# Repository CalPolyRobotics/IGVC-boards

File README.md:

# IGVC-boards
IGVC schematic and board files

.gitignore is set to only allow uploads of .sch, .brd, and .lib files.

Do not modify folders with "Final" in the name.

Pro tips:

1. Clone this repository to your computer. You need git.

2. In Eagle, go to Options > Directories.

3. Click in the "Projects" text field and then the "Browse" button to choose a directory.

4. Select the "IGVC-boards" directory that you cloned from git.

5. Click "OK" and you should see the directory in the "Projects" list in Eagle Control Panel.

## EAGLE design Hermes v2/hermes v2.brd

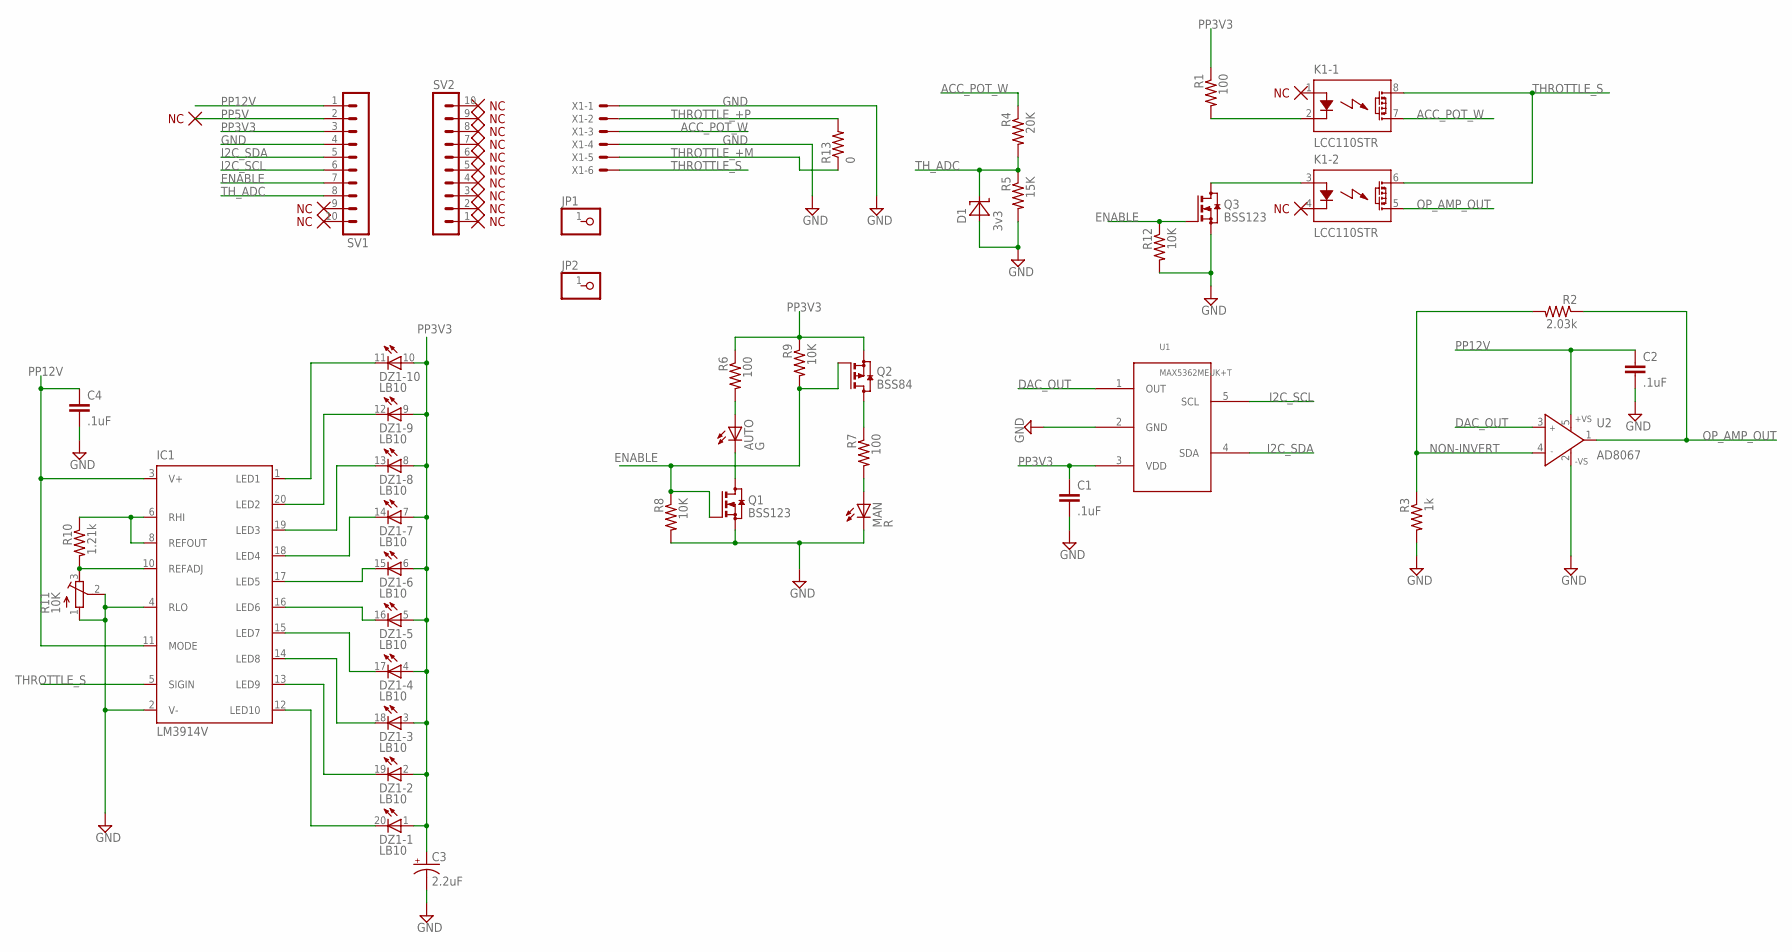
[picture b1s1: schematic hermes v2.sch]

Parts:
AUTO: G; LED_SML0603
C1, C2, C4: .1uF; C0402
C3: 2.2uF; SMC_A; DIGI 478-3119-2-ND
D1: 3v3; SOD323_ST
DZ1: LB10
IC1: LM3914V; PLCC20S
JP1, JP2: PINHD-1X1; 1X01
K1: LCC110STR; DIL08SMD
MAN: R; LED_SML0603
Q1, Q3: BSS123; SOT23
Q2: BSS84; SOT23
R1, R6, R7: 100; R0603
R2: 2.03k; R0603
R3: 1k; R0603
R4: 20K; R0603
R5: 15K; R0603
R8, R9, R12: 10K; R0603
R10: 1.21k; R0603
R11: 10K; RTRIM5X; DIGI 490-2678-1-ND
R13: 0; R0402
SV1, SV2: MA10-1
U1: DAC; SOT23-5
U2: AD8067; SOT23-5; DIGI 497-13051-1-ND
X1: 22-23-2061

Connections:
ACC_POT_W: K1.7 (D2), R4.1, X1.3
CONTROL_+: K1.2 (K), R1.2
CONTROL_-: K1.3 (A), Q3.3 (D)
DAC_OUT: U1.1 (OUT), U2.3 (IN+)
ENABLE: Q1.1 (G), Q2.1 (G), Q3.1 (G), R8.1, R9.2, R12.1, SV1.7
GND: C1.2, C2.2, C3.-, C4.2, D1.A, IC1.2 (V-), IC1.4 (RLO), MAN.C, Q1.2 (S), Q3.2 (S), R3.2, R5.2, R8.2, R11.1 (A), R11.2 (S), R12.2, SV1.4, U1.2 (GND), U2.2 (-VS), X1.1, X1.4
I2C_SCL: SV1.6, U1.5 (SCL)
I2C_SDA: SV1.5, U1.4 (SDA)
unnamed: DZ1.11 (C), IC1.1 (LED1)
unnamed: AUTO.C, Q1.3 (D)
unnamed: MAN.A, R7.2
unnamed: AUTO.A, R6.2
unnamed: Q2.3 (D), R7.1
unnamed: DZ1.12 (C), IC1.20 (LED2)
unnamed: DZ1.13 (C), IC1.19 (LED3)
unnamed: DZ1.14 (C), IC1.18 (LED4)
unnamed: DZ1.15 (C), IC1.17 (LED5)
unnamed: DZ1.16 (C), IC1.16 (LED6)
unnamed: DZ1.17 (C), IC1.15 (LED7)
unnamed: DZ1.18 (C), IC1.14 (LED8)
unnamed: DZ1.19 (C), IC1.13 (LED9)
unnamed: DZ1.20 (C), IC1.12 (LED10)
unnamed: IC1.10 (REFADJ), R10.2, R11.3 (E)
unnamed: IC1.6 (RHI), IC1.8 (REFOUT), R10.1
NON-INVERT: R2.2, R3.1, U2.4 (IN-)
OP_AMP_OUT: K1.5 (D2), R2.1, U2.1 (OUT)
PP3V3: C1.1, C3.+, DZ1.1 (A), DZ1.2 (A), DZ1.3 (A), DZ1.4 (A), DZ1.5 (A), DZ1.6 (A), DZ1.7 (A), DZ1.8 (A), DZ1.9 (A), DZ1.10 (A), Q2.2 (S), R1.1, R6.1, R9.1, SV1.3, U1.3 (VDD)
PP5V: SV1.2
PP12V: C2.1, C4.1, IC1.3 (V+), IC1.11 (MODE), SV1.1, U2.5 (+VS)
THROTTLE_+M: R13.1, X1.5
THROTTLE_+P: R13.2, X1.2
THROTTLE_S: IC1.5 (SIGIN), K1.6 (D1), K1.8 (D1), X1.6
TH_ADC: D1.C, R4.2, R5.1, SV1.8

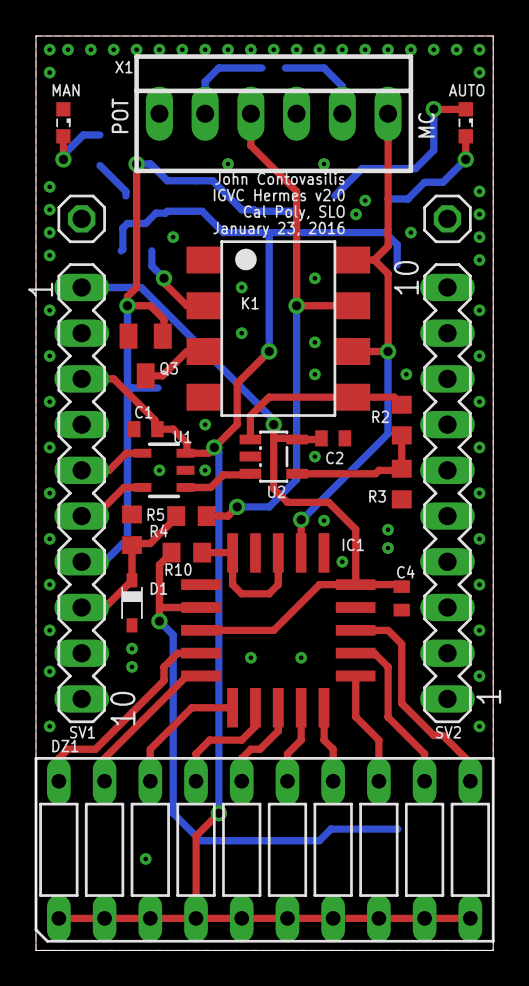
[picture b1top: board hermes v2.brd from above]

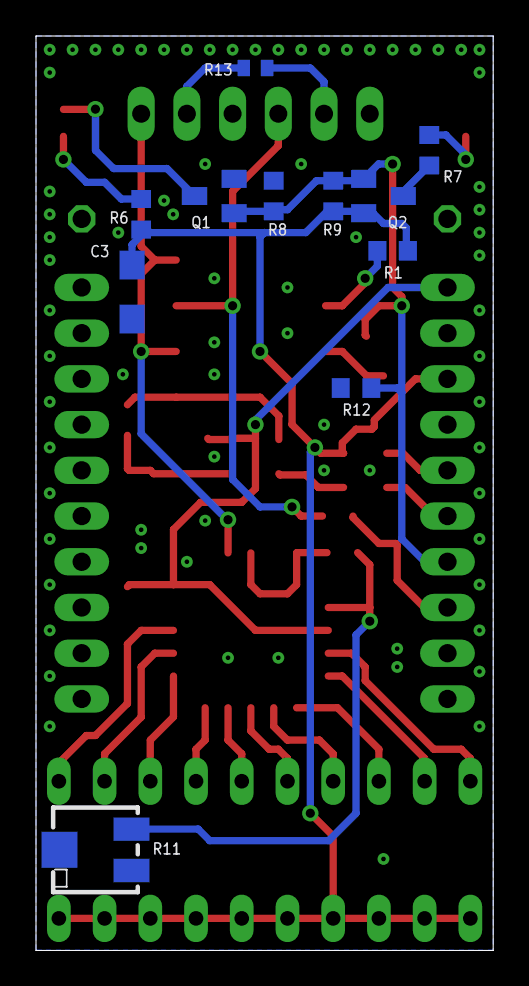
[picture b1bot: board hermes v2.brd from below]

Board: 2 copper layers, 25.4 x 50.8 mm, 33 parts (11 on the bottom side), 32 nets.

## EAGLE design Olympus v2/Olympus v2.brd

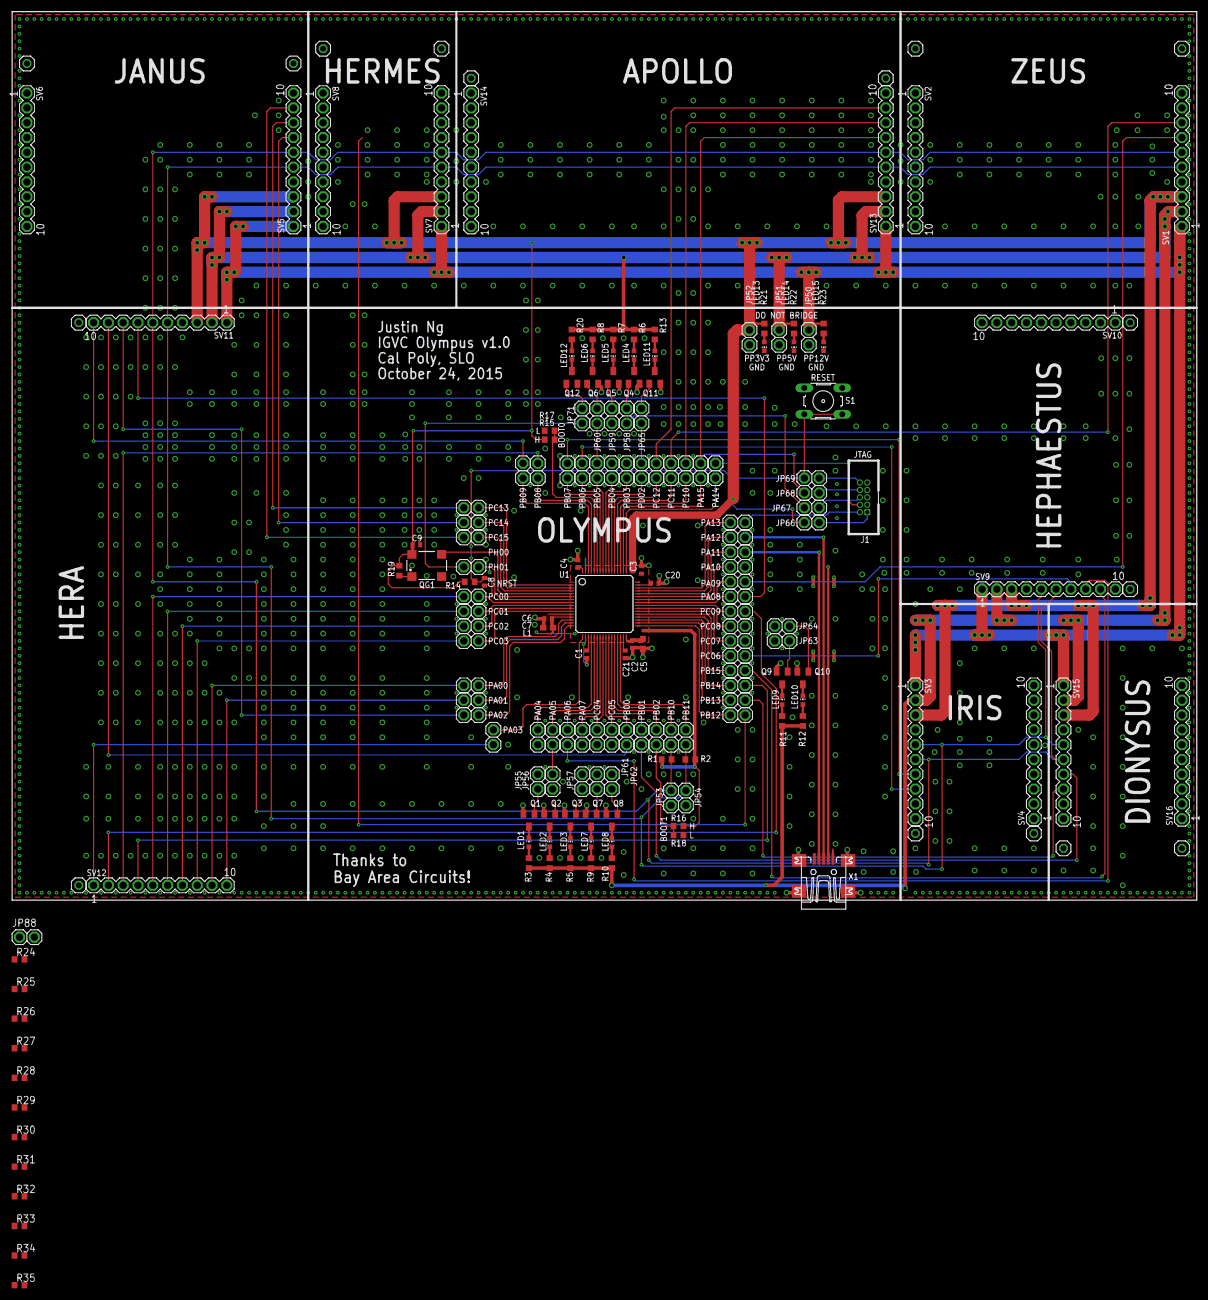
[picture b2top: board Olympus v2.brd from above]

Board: 2 copper layers, 203.2 x 152.4 mm, 183 parts (0 on the bottom side), 144 nets.

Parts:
C1, C2, C3, C4, C6, C8, C9: 0.1uF; C0402
C5: 4.7uF; C0603
C7: 1uF; C0603
C20, C21: 2.2uF; C0402
J1: HEADER_10P_0.05
JP1, JP2, JP3, JP4, JP5, JP6, JP7, JP8, JP9, JP10, JP11, JP12, JP13, JP14, JP15, JP16, JP17, JP18, JP19, JP20, JP21, JP22, JP23, JP24, JP25, JP26, JP27, JP28, JP29, JP30, JP31, JP32, JP33, JP34, JP35, JP36, JP37, JP38, JP39, JP40, JP41, JP42, JP43, JP44, JP45, JP46, JP47, JP48, JP49, JP50, JP51, JP52, JP53, JP54, JP55, JP56, JP57, JP58, JP59, JP60, JP61, JP62, JP63, JP64, JP65, JP66, JP67, JP68, JP69, JP70, JP71, JP88: 1X02
JP72, JP73, JP74, JP75, JP76, JP77, JP78, JP79, JP80, JP81, JP82, JP83, JP84, JP85, JP86, JP87: 1X01
L1: L0201
LED1, LED2, LED3, LED4, LED5, LED6, LED7, LED8, LED9, LED10, LED11, LED12, LED13, LED14, LED15: CHIP-LED0603
Q1, Q2, Q3, Q4, Q5, Q6, Q7, Q8, Q9, Q10, Q11, Q12: BSS138; SOT23
QG1: KC7050A20.0000C3GE00; SM77H
R1, R2: 3.3k; R0603
R3, R4, R5, R6, R7, R8, R9, R10, R11, R12, R13, R20: 1k; R0603
R14, R15, R16, R17, R18, R19, R24, R25, R26, R27, R28, R29, R30, R31, R32, R33, R34, R35: 10k; R0603
R21: 82; R0603
R22: 200; R0603
R23: 680; R0603
S1: B3F-10XX
SV1, SV2, SV3, SV4, SV5, SV6, SV7, SV8, SV9, SV10, SV11, SV12, SV13, SV14, SV15, SV16: MA10-1
U1: STM32F205RGT6; LQFP-ST-64-2
X1: MINI-USB-UX60-MB-5ST; UX60-MB-5ST

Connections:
APOLLO_SPI_MOSI: JP45.2, SV13.9
APOLLO_SPI_SCK: JP43.2, SV13.8
APOLLO_SPI_SS_N: JP16.1, JP68.2, SV13.7
DIONYSUS_BRD_EN: JP18.1, SV15.7
DIONYSUS_GPIO: JP30.1, SV15.8
GND: C1.2, C2.2, C3.2, C4.2, C5.2, C6.2, C7.2, C8.2, C9.2, C20.2, C21.2, J1.3, J1.5, JP50.2, JP51.2, JP52.2, JP53.2, JP54.2, LED13.C, LED14.C, LED15.C, Q1.2, Q2.2, Q3.2, Q4.2, Q5.2, Q6.2, Q7.2, Q8.2, Q9.2, Q10.2, Q11.2, Q12.2, QG1.2, R17.1, R18.1, R24.2, R25.2, R26.2, R27.2, R28.2, R29.2, R30.2, R31.2, R32.2, R33.2, R34.2, R35.2, S1.3, S1.4, SV1.4, SV3.4, SV5.4, SV7.4, SV9.4, SV11.4, SV13.4, SV15.4, U1.12, U1.18, U1.63, X1.5
HEPHAESTUS_DIR: JP39.2, SV9.7
HEPHAESTUS_GPIO: JP32.1, SV9.9
HEPHAESTUS_SPD: JP7.1, SV9.8
HERA_HALL1: JP25.1, SV12.3
HERA_HALL2: JP31.1, JP42.2, SV12.4
HERA_SONAR1: JP9.1, SV11.7
HERA_SONAR2: JP3.1, SV11.8
HERA_SONAR3: JP17.1, SV11.9
HERA_SONAR4: JP26.1, SV11.10
HERA_SONAR5: JP4.1, SV12.1
HERA_STEER: JP33.2, SV12.5
HERA_TEMP1: JP34.2, SV12.6
HERA_TEMP2: JP35.2, SV12.7
HERA_TEMP3: JP36.2, SV12.8
HERA_TEMP4: JP1.1, SV12.9
HERA_TEMP5: JP2.1, SV12.10
I2C_SCL: JP27.1, JP53.1, R1.1, SV1.6, SV3.6, SV5.6, SV7.6, SV9.6, SV11.6, SV13.6, SV15.6
I2C_SDA: JP28.1, JP54.1, R2.1, SV1.5, SV3.5, SV5.5, SV7.5, SV9.5, SV11.5, SV13.5, SV15.5
IRIS_UART_RX: JP24.1, SV3.7
IRIS_UART_TX: JP23.1, SV3.8
JANUS_AUTOMAN: JP48.2, SV5.9
JANUS_F: JP47.2, SV5.7
JANUS_R: JP46.2, SV5.8
JTAG_NRST: J1.10, JP69.1
JTAG_SWO: J1.6, JP67.1
JTAG_TDI: J1.8, JP68.1
JTAG_VREF: J1.1, JP66.2
LED1_A: LED1.A, R3.1
LED1_C: LED1.C, Q1.3
LED1_G: JP55.1, Q1.1, R24.1
LED2_A: LED2.A, R4.1
LED2_C: LED2.C, Q2.3
LED2_G: JP56.1, Q2.1, R25.1
LED3_A: LED3.A, R5.1
LED3_C: LED3.C, Q3.3
LED3_G: JP57.1, Q3.1, R26.1
LED4_A: LED4.A, R6.1
LED4_C: LED4.C, Q4.3
LED4_G: JP58.1, Q4.1, R27.1
LED5_A: LED5.A, R7.1
LED5_C: LED5.C, Q5.3
LED5_G: JP59.1, Q5.1, R32.1
LED6_A: LED6.A, R8.1
LED6_C: LED6.C, Q6.3
LED6_G: JP60.1, Q6.1, R33.1
LED7_A: LED7.A, R9.1
LED7_C: LED7.C, Q7.3
LED7_G: JP61.1, Q7.1, R34.1
LED8_A: LED8.A, R10.1
LED8_C: LED8.C, Q8.3
LED8_G: JP62.1, Q8.1, R35.1
LED9_A: LED9.A, R11.1
LED9_C: LED9.C, Q9.3
LED9_G: JP63.1, Q9.1, R28.1
LED10_A: LED10.A, R12.1
LED10_C: LED10.C, Q10.3
LED10_G: JP64.1, Q10.1, R29.1
LED11_A: LED11.A, R13.1
LED11_C: LED11.C, Q11.3
LED11_G: JP65.1, Q11.1, R30.1
LED12_A: LED12.A, R20.1
LED12_C: LED12.C, Q12.3
LED12_G: JP71.1, Q12.1, R31.1
LED13_R: LED13.A, R21.1
LED14_R: LED14.A, R22.1
LED15_R: LED15.A, R23.1
MCU_BOOT0: JP88.1, R15.1, R17.2, U1.60
MCU_BOOT1: JP19.1, R16.1, R18.2
MCU_NRST: C8.1, JP69.2, R14.1, S1.1, S1.2, U1.7
MCU_PA0: JP1.2, U1.14
MCU_PA1: JP2.2, U1.15
MCU_PA2: JP3.2, U1.16
MCU_PA3: JP4.2, U1.17
MCU_PA4: JP5.2, U1.20
MCU_PA5: JP6.2, U1.21
MCU_PA6: JP7.2, U1.22
MCU_PA7: JP8.2, U1.23
MCU_PA8: JP9.2, U1.41
MCU_PA9: JP10.2, U1.42
MCU_PA10: JP11.2, U1.43
MCU_PA11: JP12.2, U1.44
MCU_PA12: JP13.2, U1.45
MCU_PA13: JP14.2, U1.46
MCU_PA14: JP15.2, U1.49
MCU_PA15: JP16.2, U1.50
MCU_PB0: JP17.2, U1.26
MCU_PB1: JP18.2, U1.27
MCU_PB2: JP19.2, U1.28
MCU_PB3: JP20.2, U1.55
MCU_PB4: JP21.2, U1.56
MCU_PB5: JP22.2, U1.57
MCU_PB6: JP23.2, U1.58
MCU_PB7: JP24.2, U1.59
MCU_PB8: JP25.2, U1.61
MCU_PB9: JP26.2, U1.62
MCU_PB10: JP27.2, U1.29
MCU_PB11: JP28.2, U1.30
MCU_PB12: JP29.2, U1.33
MCU_PB13: JP30.2, U1.34
MCU_PB14: JP31.2, U1.35
MCU_PB15: JP32.2, U1.36
MCU_PC0: JP33.1, U1.8
MCU_PC1: JP34.1, U1.9
MCU_PC2: JP35.1, U1.10
MCU_PC3: JP36.1, U1.11
MCU_PC4: JP37.1, U1.24
MCU_PC5: JP38.1, U1.25
MCU_PC6: JP39.1, U1.37
MCU_PC7: JP40.1, U1.38
MCU_PC8: JP41.1, U1.39
MCU_PC9: JP42.1, U1.40
MCU_PC10: JP43.1, U1.51
MCU_PC11: JP44.1, U1.52
MCU_PC12: JP45.1, U1.53
MCU_PC13: JP46.1, U1.2
MCU_PC14: JP47.1, U1.3
MCU_PC15: JP48.1, U1.4
MCU_PD2: JP49.1, U1.54
MCU_PH0: QG1.3, U1.5
MCU_PH1: JP70.1, U1.6
MCU_VCAP_1: C21.1, U1.31
MCU_VCAP_2: C20.1, U1.47
OLYMPUS_GPIO2: JP6.1, JP56.2
OLYMPUS_GPIO4: JP58.2, JP67.2
OLYMPUS_GPIO6: JP22.1, JP60.2
OLYMPUS_GPIO11: JP49.2, JP65.2
OLYMPUS_GPIO12: JP70.2, JP71.2
OLYMPUS_SWDCLK: J1.4, JP15.1
OLYMPUS_SWDIO: J1.2, JP14.1
OLYMPUS_USBDN: JP12.1, X1.2
OLYMPUS_USBDP: JP13.1, X1.3
OSC_EN: QG1.1, R19.1
PP3V3: C1.1, C2.1, C3.1, C4.1, C5.1, C9.1, JP52.1, JP66.1, L1.2, QG1.4, R1.2, R2.2, R14.2, R15.2, R16.2, R19.2, R21.2, SV1.3, SV3.3, SV5.3, SV7.3, SV9.3, SV11.3, SV13.3, SV15.3, U1.19, U1.32, U1.48, U1.64
PP3V3A: C6.1, C7.1, L1.1, U1.13
PP5V: JP51.1, R3.2, R4.2, R5.2, R6.2, R7.2, R8.2, R9.2, R10.2, R11.2, R12.2, R13.2, R20.2, R22.2, SV1.2, SV3.2, SV5.2, SV7.2, SV9.2, SV11.2, SV13.2, SV15.2
PP12V: JP50.1, R23.2, SV1.1, SV3.1, SV5.1, SV7.1, SV9.1, SV11.1, SV13.1, SV15.1
ZEUS_GPIO: JP44.2, SV1.8
ZEUS_SHUTDOWN_N: JP10.1, SV1.7

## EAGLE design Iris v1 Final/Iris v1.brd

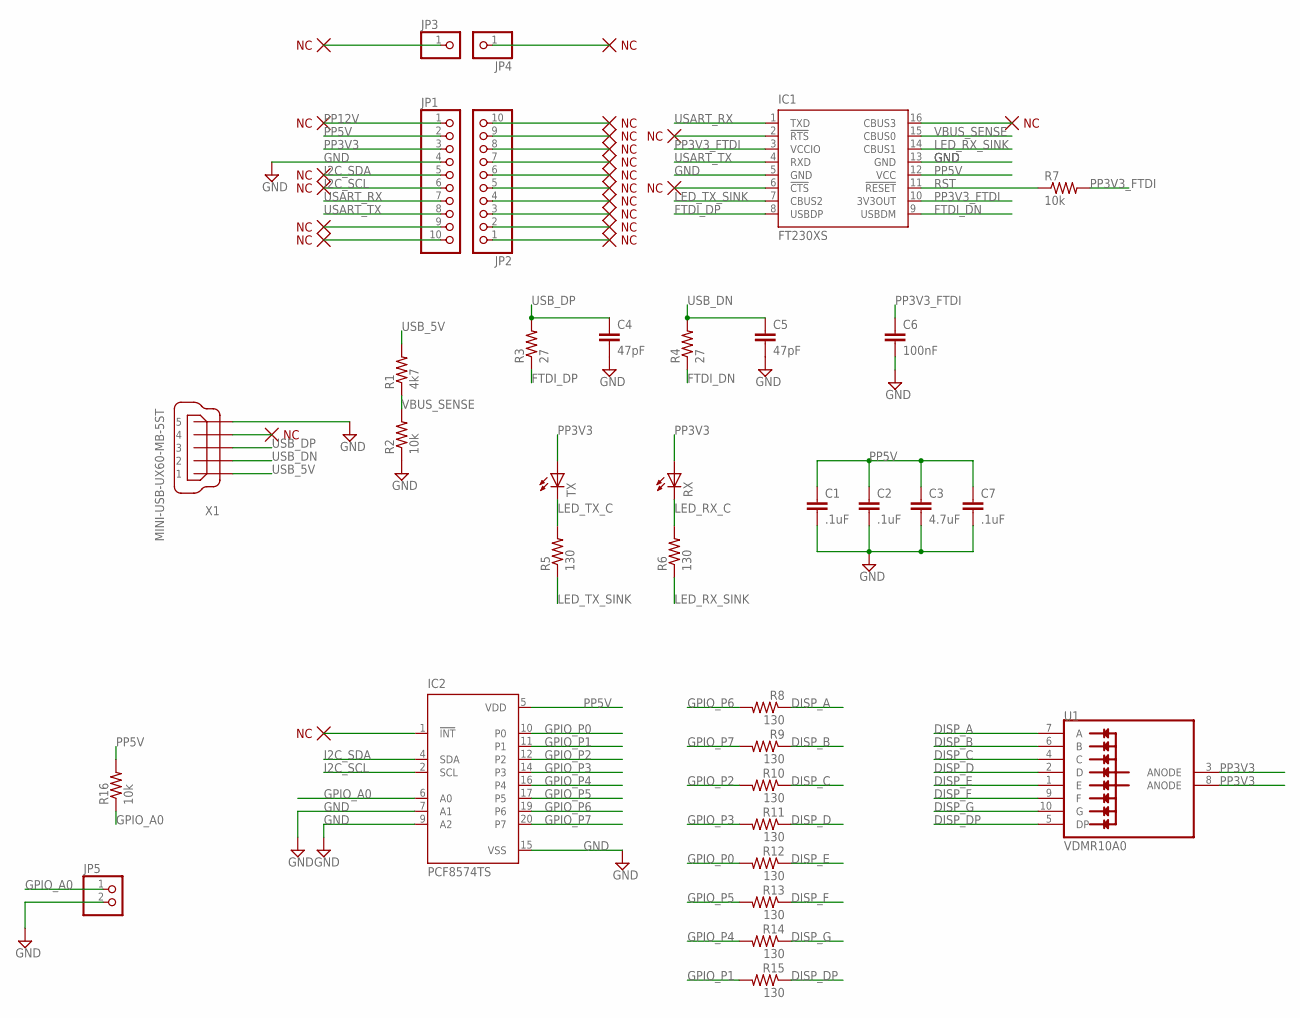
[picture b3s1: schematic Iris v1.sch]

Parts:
C1, C2, C7: .1uF; C0402
C3: 4.7uF; C0603
C4, C5: 47pF; C0402
C6: 100nF; C0402
IC1: FT230XS; SSOP16; DIGI 768-1135-1-ND
IC2: PCF8574TS; SSOP20; DIGI 568-8246-1-ND
JP1, JP2: PINHD-1X10; 1X10
JP3, JP4: PINHD-1X1; 1X01
JP5: PINHD-1X2; 1X02
R1: 4k7; R0402
R2, R16: 10k; R0402
R3, R4: 27; R0402
R5, R6, R8, R9, R10, R11, R12, R13, R14, R15: 130; R0402
R7: 10k; R0603
RX: LEDCHIP-LED0603; CHIP-LED0603; DIGI 160-1434-1-ND
TX: LEDCHIP-LED0603; CHIP-LED0603; DIGI 160-1434-1-ND
U1: VDMR10.0; VDMR10A0
X1: MINI-USB-UX60-MB-5ST; UX60-MB-5ST; DIGI H2959CT-ND

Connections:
DISP_A: R8.1, U1.7 (A)
DISP_B: R9.1, U1.6 (B)
DISP_C: R10.1, U1.4 (C)
DISP_D: R11.1, U1.2 (D)
DISP_DP: R15.1, U1.5 (DP)
DISP_E: R12.1, U1.1 (E)
DISP_F: R13.1, U1.9 (F)
DISP_G: R14.1, U1.10 (G)
FTDI_DN: IC1.9 (USBDM), R4.1
FTDI_DP: IC1.8 (USBDP), R3.1
GND: C1.2, C2.2, C3.2, C4.2, C5.2, C6.2, C7.2, IC1.5 (GND), IC1.13 (GND), IC2.7 (A1), IC2.9 (A2), IC2.15 (VSS), JP1.4, JP5.2, R2.1, X1.5
GPIO_A0: IC2.6 (A0), JP5.1, R16.1
GPIO_P0: IC2.10 (P0), R12.2
GPIO_P1: IC2.11 (P1), R15.2
GPIO_P2: IC2.12 (P2), R10.2
GPIO_P3: IC2.14 (P3), R11.2
GPIO_P4: IC2.16 (P4), R14.2
GPIO_P5: IC2.17 (P5), R13.2
GPIO_P6: IC2.19 (P6), R8.2
GPIO_P7: IC2.20 (P7), R9.2
I2C_SCL: IC2.2 (SCL), JP1.6
I2C_SDA: IC2.4 (SDA), JP1.5
LED_RX_C: R6.2, RX.C
LED_RX_SINK: IC1.14 (CBUS1), R6.1
LED_TX_C: R5.2, TX.C
LED_TX_SINK: IC1.7 (CBUS2), R5.1
PP3V3: JP1.3, RX.A, TX.A, U1.3 (ANODE), U1.8 (ANODE)
PP3V3_FTDI: C6.1, IC1.3 (VCCIO), IC1.10 (3V3OUT), R7.2
PP5V: C1.1, C2.1, C3.1, C7.1, IC1.12 (VCC), IC2.5 (VDD), JP1.2, R16.2
PP12V: JP1.1
RST: IC1.11 (!RESET), R7.1
USART_RX: IC1.1 (TXD), JP1.7
USART_TX: IC1.4 (RXD), JP1.8
USB_5V: R1.2, X1.1
USB_DN: C5.1, R4.2, X1.2
USB_DP: C4.1, R3.2, X1.3
VBUS_SENSE: IC1.15 (CBUS0), R1.1, R2.2

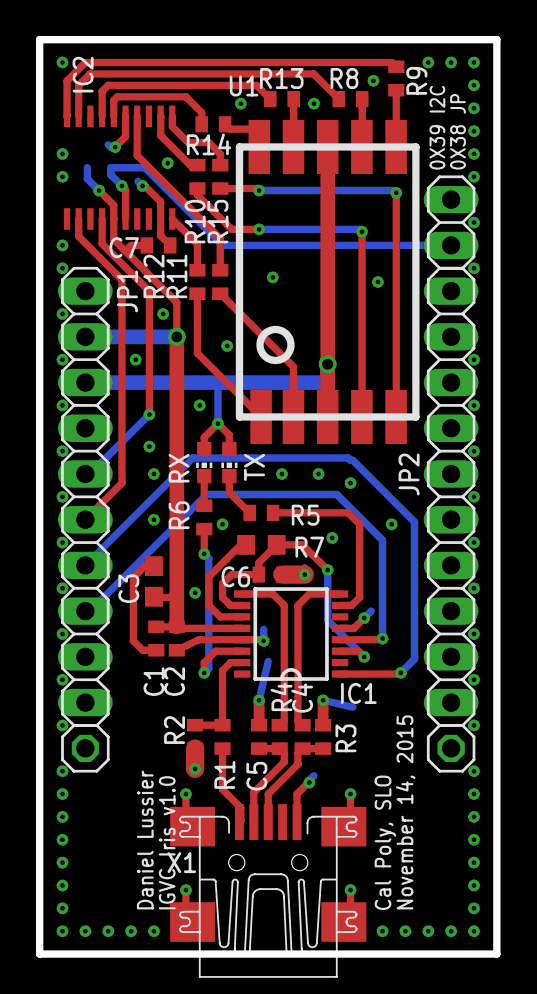
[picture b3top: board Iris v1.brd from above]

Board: 2 copper layers, 25.4 x 50.8 mm, 34 parts (1 on the bottom side), 36 nets.

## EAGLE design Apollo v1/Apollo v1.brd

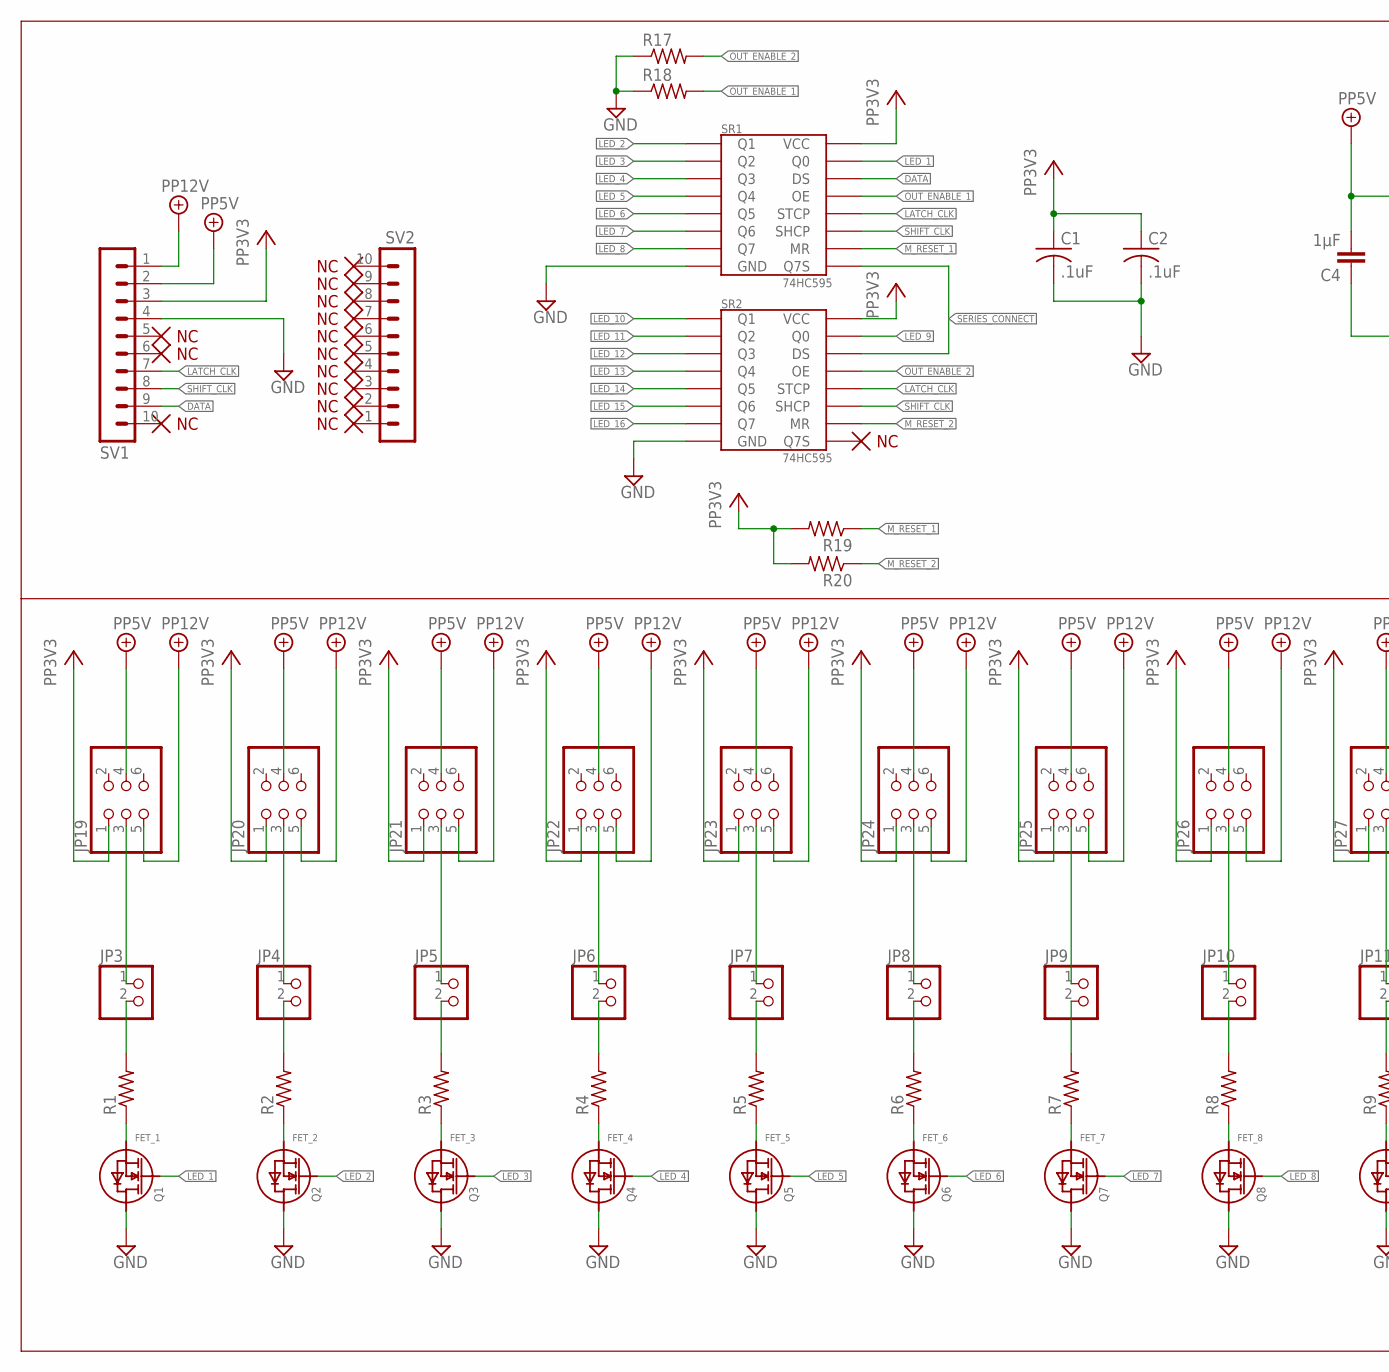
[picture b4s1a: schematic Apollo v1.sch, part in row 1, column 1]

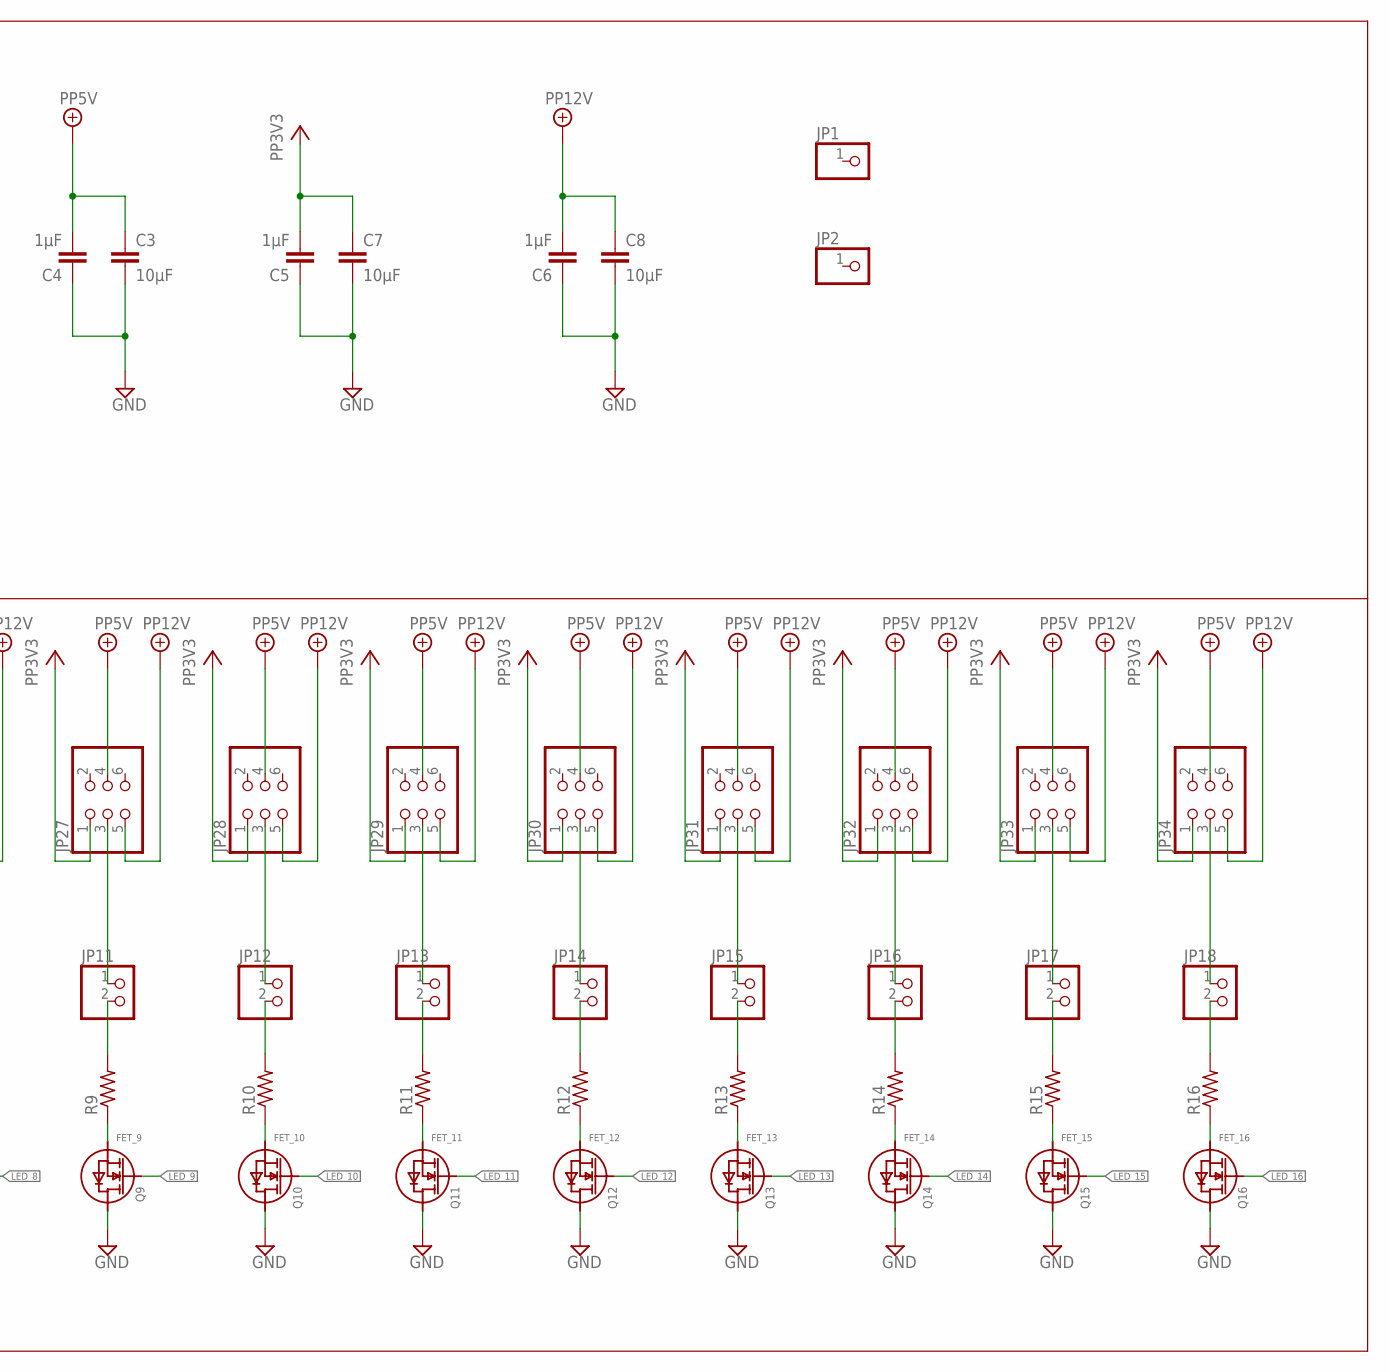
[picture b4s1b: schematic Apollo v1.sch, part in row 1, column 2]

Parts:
C1, C2: .1uF; C0603
C3, C7, C8: 10μF; C1206
C4, C5, C6: 1μF; C0603
JP1, JP2: PINHD-1X1; 1X01
JP3, JP4, JP5, JP6, JP7, JP8, JP9, JP10, JP11, JP12, JP13, JP14, JP15, JP16, JP17, JP18: PINHD-1X2; 1X02
JP19, JP20, JP21, JP22, JP23, JP24, JP25, JP26, JP27, JP28, JP29, JP30, JP31, JP32, JP33, JP34: PINHD-2X3; 2X03
Q1, Q2, Q3, Q4, Q5, Q6, Q7, Q8, Q9, Q10, Q11, Q12, Q13, Q14, Q15, Q16: DMN6140L-7; SOT-23-3
R1, R2, R3, R4, R5, R6, R7, R8, R9, R10, R11, R12, R13, R14, R15, R16, R17, R18, R19, R20: R-US_R1206; R1206
SR1, SR2: 74HC595; SO-16
SV1, SV2: MA10-1

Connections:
DATA: SR1.P$14 (DS), SV1.9
FET_1: Q1.P$2 (S), R1.1
FET_2: Q2.P$2 (S), R2.1
FET_3: Q3.P$2 (S), R3.1
FET_4: Q4.P$2 (S), R4.1
FET_5: Q5.P$2 (S), R5.1
FET_6: Q6.P$2 (S), R6.1
FET_7: Q7.P$2 (S), R7.1
FET_8: Q8.P$2 (S), R8.1
FET_9: Q9.P$2 (S), R9.1
FET_10: Q10.P$2 (S), R10.1
FET_11: Q11.P$2 (S), R11.1
FET_12: Q12.P$2 (S), R12.1
FET_13: Q13.P$2 (S), R13.1
FET_14: Q14.P$2 (S), R14.1
FET_15: Q15.P$2 (S), R15.1
FET_16: Q16.P$2 (S), R16.1
GND: C1.2, C2.2, C3.2, C4.1, C5.1, C6.1, C7.2, C8.2, Q1.P$3 (D), Q2.P$3 (D), Q3.P$3 (D), Q4.P$3 (D), Q5.P$3 (D), Q6.P$3 (D), Q7.P$3 (D), Q8.P$3 (D), Q9.P$3 (D), Q10.P$3 (D), Q11.P$3 (D), Q12.P$3 (D), Q13.P$3 (D), Q14.P$3 (D), Q15.P$3 (D), Q16.P$3 (D), R17.1, R18.1, SR1.P$8 (GND), SR2.P$8 (GND), SV1.4
LATCH_CLK: SR1.P$12 (STCP), SR2.P$12 (STCP), SV1.7
LED_1: Q1.P$1 (G), SR1.P$15 (Q0)
LED_2: Q2.P$1 (G), SR1.P$1 (Q1)
LED_3: Q3.P$1 (G), SR1.P$2 (Q2)
LED_4: Q4.P$1 (G), SR1.P$3 (Q3)
LED_5: Q5.P$1 (G), SR1.P$4 (Q4)
LED_6: Q6.P$1 (G), SR1.P$5 (Q5)
LED_7: Q7.P$1 (G), SR1.P$6 (Q6)
LED_8: Q8.P$1 (G), SR1.P$7 (Q7)
LED_9: Q9.P$1 (G), SR2.P$15 (Q0)
LED_10: Q10.P$1 (G), SR2.P$1 (Q1)
LED_11: Q11.P$1 (G), SR2.P$2 (Q2)
LED_12: Q12.P$1 (G), SR2.P$3 (Q3)
LED_13: Q13.P$1 (G), SR2.P$4 (Q4)
LED_14: Q14.P$1 (G), SR2.P$5 (Q5)
LED_15: Q15.P$1 (G), SR2.P$6 (Q6)
LED_16: Q16.P$1 (G), SR2.P$7 (Q7)
M_RESET_1: R19.1, SR1.P$10 (MR)
M_RESET_2: R20.1, SR2.P$10 (MR)
unnamed: JP3.2, R1.2
unnamed: JP4.2, R2.2
unnamed: JP5.2, R3.2
unnamed: JP6.2, R4.2
unnamed: JP7.2, R5.2
unnamed: JP8.2, R6.2
unnamed: JP9.2, R7.2
unnamed: JP10.2, R8.2
unnamed: JP11.2, R9.2
unnamed: JP12.2, R10.2
unnamed: JP13.2, R11.2
unnamed: JP14.2, R12.2
unnamed: JP15.2, R13.2
unnamed: JP16.2, R14.2
unnamed: JP17.2, R15.2
unnamed: JP18.2, R16.2
unnamed: JP3.1, JP19.3
unnamed: JP4.1, JP20.3
unnamed: JP5.1, JP21.3
unnamed: JP6.1, JP22.3
unnamed: JP7.1, JP23.3
unnamed: JP8.1, JP24.3
unnamed: JP9.1, JP25.3
unnamed: JP10.1, JP26.3
unnamed: JP11.1, JP27.3
unnamed: JP12.1, JP28.3
unnamed: JP13.1, JP29.3
unnamed: JP14.1, JP30.3
unnamed: JP15.1, JP31.3
unnamed: JP16.1, JP32.3
unnamed: JP17.1, JP33.3
unnamed: JP18.1, JP34.3
OUT_ENABLE_1: R18.2, SR1.P$13 (OE)
OUT_ENABLE_2: R17.2, SR2.P$13 (OE)
PP3V3: C1.1, C2.1, C5.2, C7.1, JP19.1, JP20.1, JP21.1, JP22.1, JP23.1, JP24.1, JP25.1, JP26.1, JP27.1, JP28.1, JP29.1, JP30.1, JP31.1, JP32.1, JP33.1, JP34.1, R19.2, R20.2, SR1.P$16 (VCC), SR2.P$16 (VCC), SV1.3
PP5V: C3.1, C4.2, JP19.4, JP20.4, JP21.4, JP22.4, JP23.4, JP24.4, JP25.4, JP26.4, JP27.4, JP28.4, JP29.4, JP30.4, JP31.4, JP32.4, JP33.4, JP34.4, SV1.2
PP12V: C6.2, C8.1, JP19.5, JP20.5, JP21.5, JP22.5, JP23.5, JP24.5, JP25.5, JP26.5, JP27.5, JP28.5, JP29.5, JP30.5, JP31.5, JP32.5, JP33.5, JP34.5, SV1.1
SERIES_CONNECT: SR1.P$9 (Q7S), SR2.P$14 (DS)
SHIFT_CLK: SR1.P$11 (SHCP), SR2.P$11 (SHCP), SV1.8

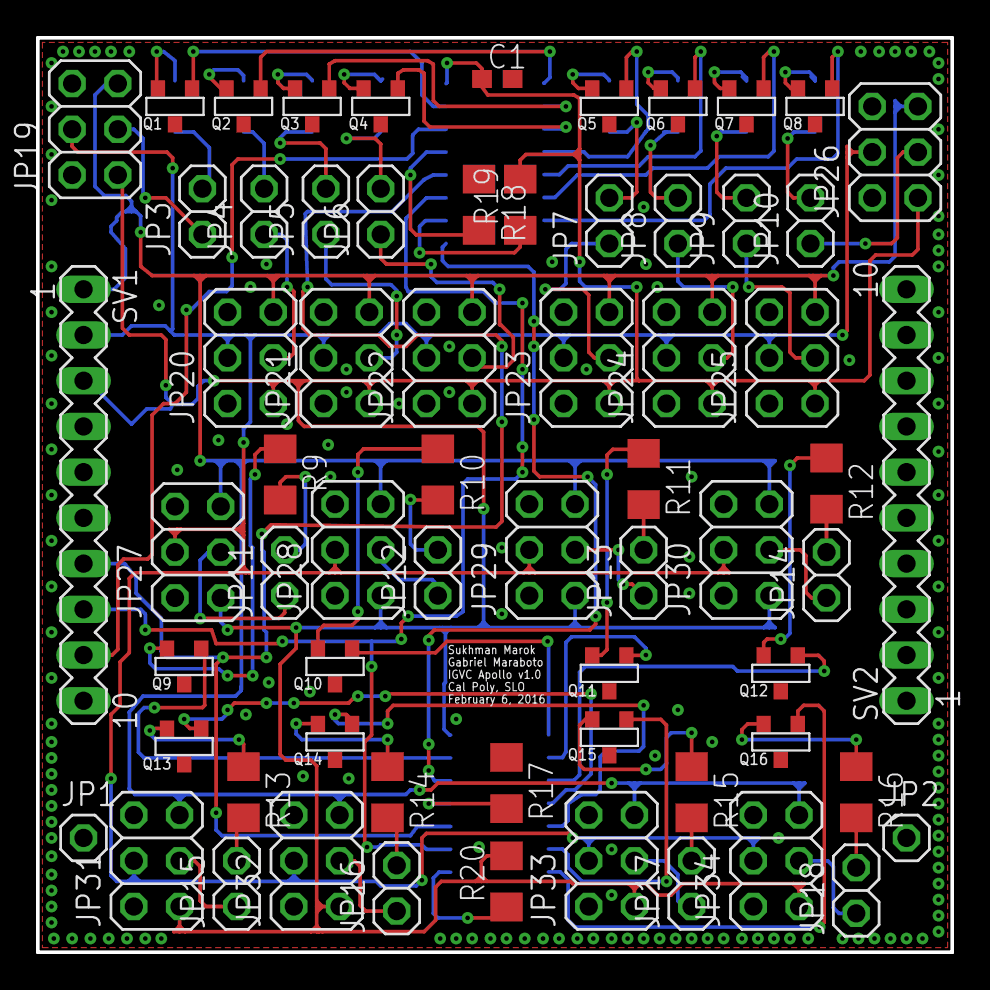
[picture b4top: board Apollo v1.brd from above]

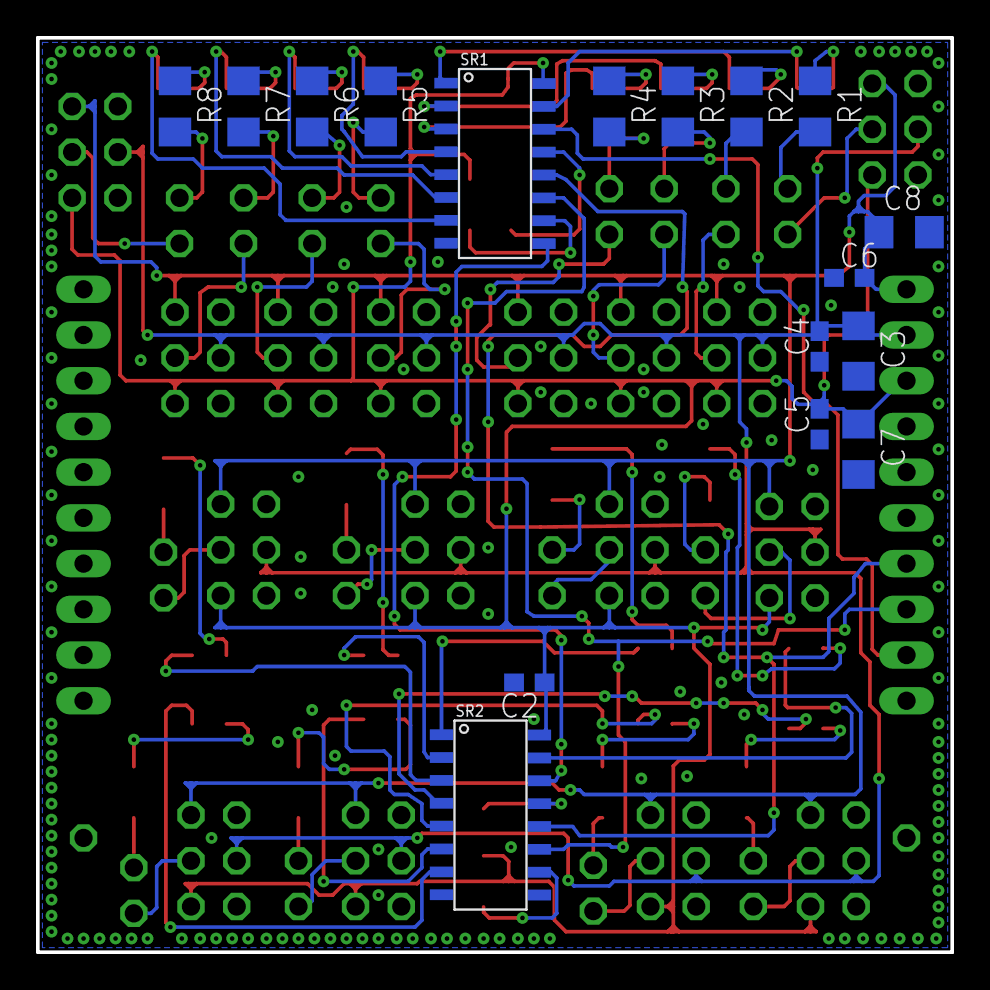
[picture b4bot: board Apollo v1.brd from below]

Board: 2 copper layers, 50.8 x 50.8 mm, 82 parts (17 on the bottom side), 76 nets.

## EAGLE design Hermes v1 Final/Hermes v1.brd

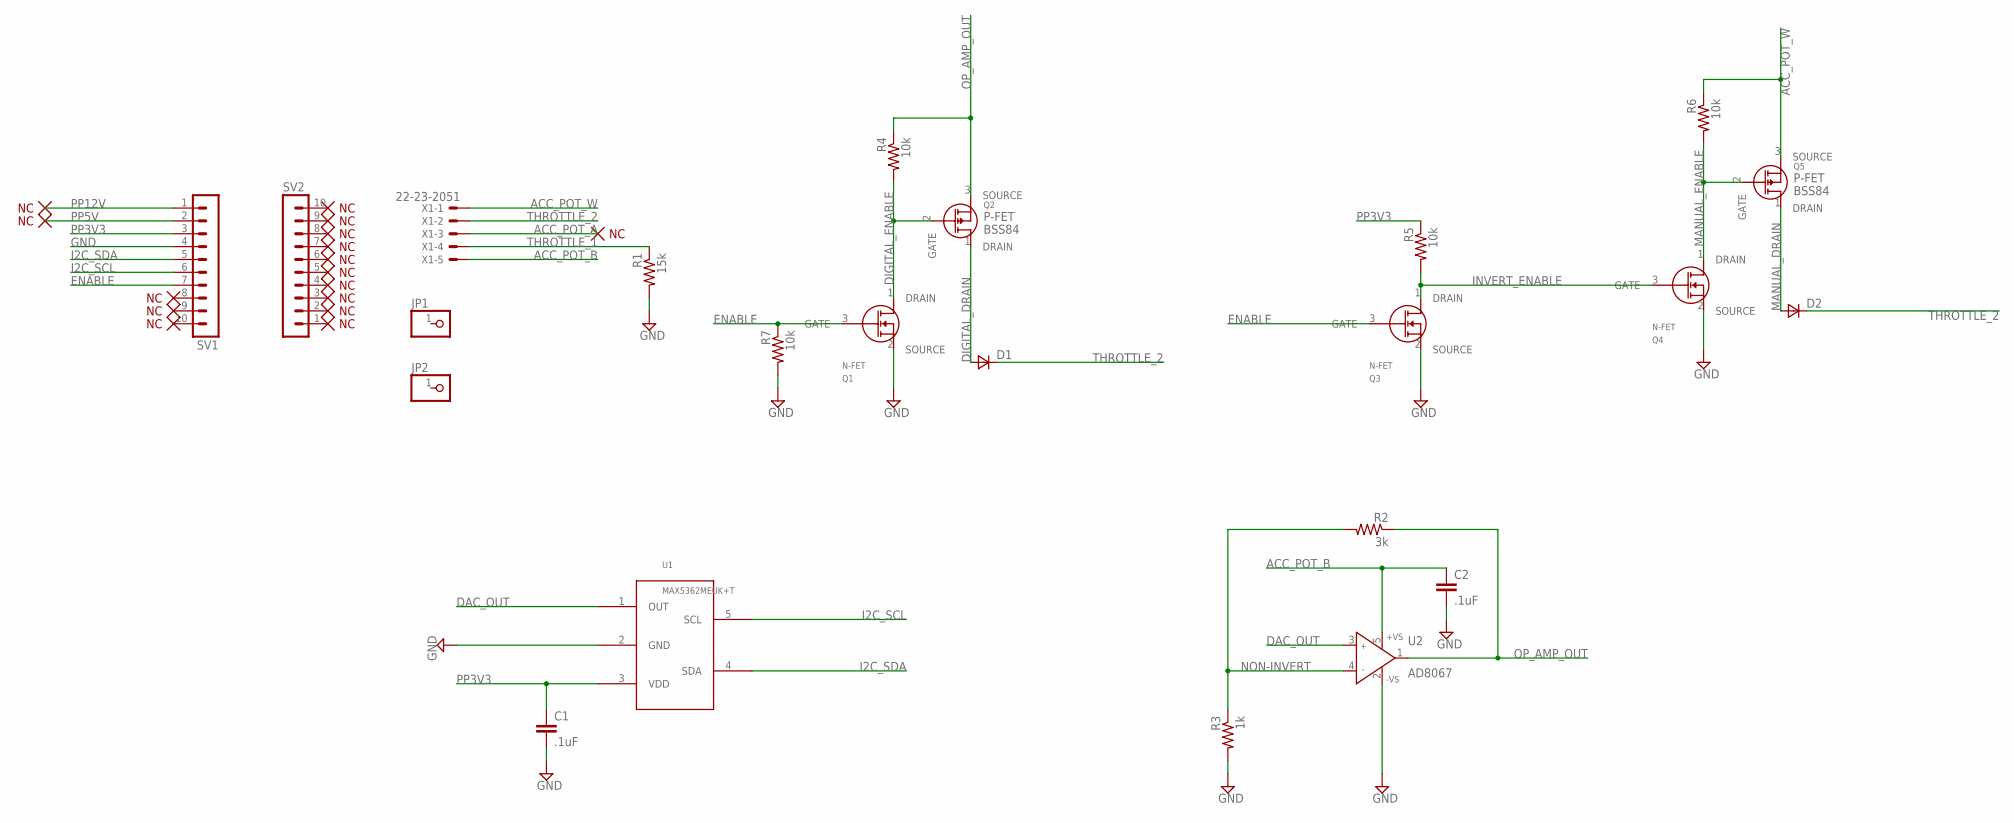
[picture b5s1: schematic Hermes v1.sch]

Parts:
C1, C2: .1uF; C0402
D1: DSOD323; SOD323; DIGI BAT54WS-FDICT-ND
D2: DSOD323; SOD323
JP1, JP2: PINHD-1X1; 1X01
Q1, Q3, Q4: NMOSFET; SOT-23
Q2, Q5: P-FET; SOT-23; DIGI BSS84CT-ND
R1: 15k; R0603
R2: 3k; R0603
R3: 1k; R0603
R4, R5, R6, R7: 10k; R0603
SV1, SV2: MA10-1
U1: DAC; SOT23-5
U2: AD8067; SOT23-5; DIGI 497-13051-1-ND
X1: 22-23-2051

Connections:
ACC_POT_A: X1.3
ACC_POT_B: C2.1, U2.5 (+VS), X1.5
ACC_POT_W: Q5.3 (SOURCE), R6.1, X1.1
DAC_OUT: U1.1 (OUT), U2.3 (IN+)
DIGITAL_DRAIN: D1.2 (A), Q2.1 (DRAIN)
DIGITAL_ENABLE: Q1.1 (DRAIN), Q2.2 (GATE), R4.2
ENABLE: Q1.3 (GATE), Q3.3 (GATE), R7.1, SV1.7
GND: C1.2, C2.2, Q1.2 (SOURCE), Q3.2 (SOURCE), Q4.2 (SOURCE), R1.2, R3.2, R7.2, SV1.4, U1.2 (GND), U2.2 (-VS)
I2C_SCL: SV1.6, U1.5 (SCL)
I2C_SDA: SV1.5, U1.4 (SDA)
INVERT_ENABLE: Q3.1 (DRAIN), Q4.3 (GATE), R5.2
MANUAL_DRAIN: D2.2 (A), Q5.1 (DRAIN)
MANUAL_ENABLE: Q4.1 (DRAIN), Q5.2 (GATE), R6.2
NON-INVERT: R2.2, R3.1, U2.4 (IN-)
OP_AMP_OUT: Q2.3 (SOURCE), R2.1, R4.1, U2.1 (OUT)
PP3V3: C1.1, R5.1, SV1.3, U1.3 (VDD)
PP5V: SV1.2
PP12V: SV1.1
THROTTLE_1: R1.1, X1.4
THROTTLE_2: D1.1 (C), D2.1 (C), X1.2

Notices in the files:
parts and their libraries:
SparkFun-Resistors: Licensing: Creative Commons ShareAlike 4.0 International - https://creativecommons.org/licenses/by-sa/4.0
